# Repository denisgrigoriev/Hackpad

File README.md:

# Minimalistic Hackpad
In this project i would be design a ultra small and minimal HackPad, this removes unnessary keys and only provides keys would would be used often, for example one key could be to copy, another paste and another could be used to screenshot and and so forth.

## Goals

- Each key would be useful.
- This project focus more on aesthetic rather than functionality.
- The whole Hackpad could fit in your hand.

## Schematic & PCB design

## £3D Model

## BOM
- 4x Cherry MX Switches
- 1x EC11 Rotary Encoder
- 1x XIAO RP2040
- 1x Case (2 printed parts)
- 4x DSA Keycaps
- 2x M3x5x4 Heatset inserts
- 2x M3x12mm SHCS Bolts

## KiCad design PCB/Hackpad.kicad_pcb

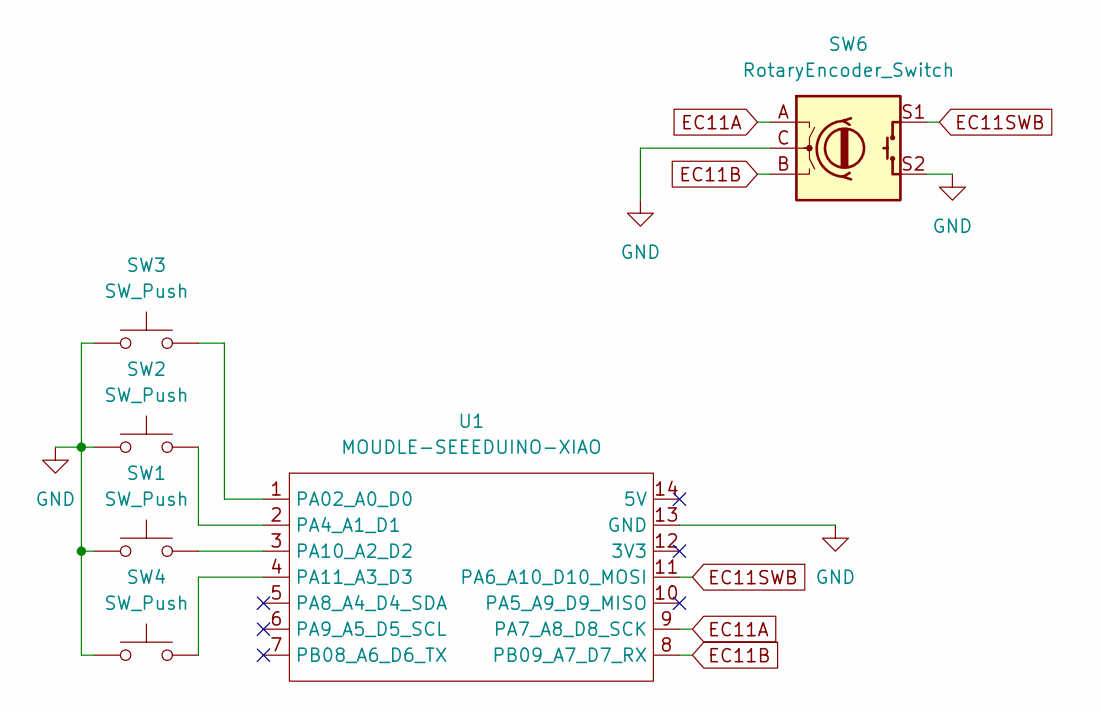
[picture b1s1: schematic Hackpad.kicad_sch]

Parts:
SW1, SW2, SW3, SW4: SW_Push; SW_Cherry_MX_1.00u_PCB
SW6: RotaryEncoder_Switch; RotaryEncoder_Alps_EC11E-Switch_Vertical_H20mm
U1: MOUDLE-SEEEDUINO-XIAO; XIAO-Generic-Hybrid-14P-2.54-21X17.8MM

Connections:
EC11A: SW6.A, U1.9 (PA7_A8_D8_SCK)
EC11B: SW6.B, U1.8 (PB09_A7_D7_RX)
EC11SWB: SW6.S1, U1.11 (PA6_A10_D10_MOSI)
GND: SW1.1, SW2.1, SW3.1, SW4.1, SW6.C, SW6.S2, U1.13 (GND)
unnamed: SW3.2, U1.1 (PA02_A0_D0)
unnamed: SW2.2, U1.2 (PA4_A1_D1)
unnamed: SW1.2, U1.3 (PA10_A2_D2)
unnamed: SW4.2, U1.4 (PA11_A3_D3)

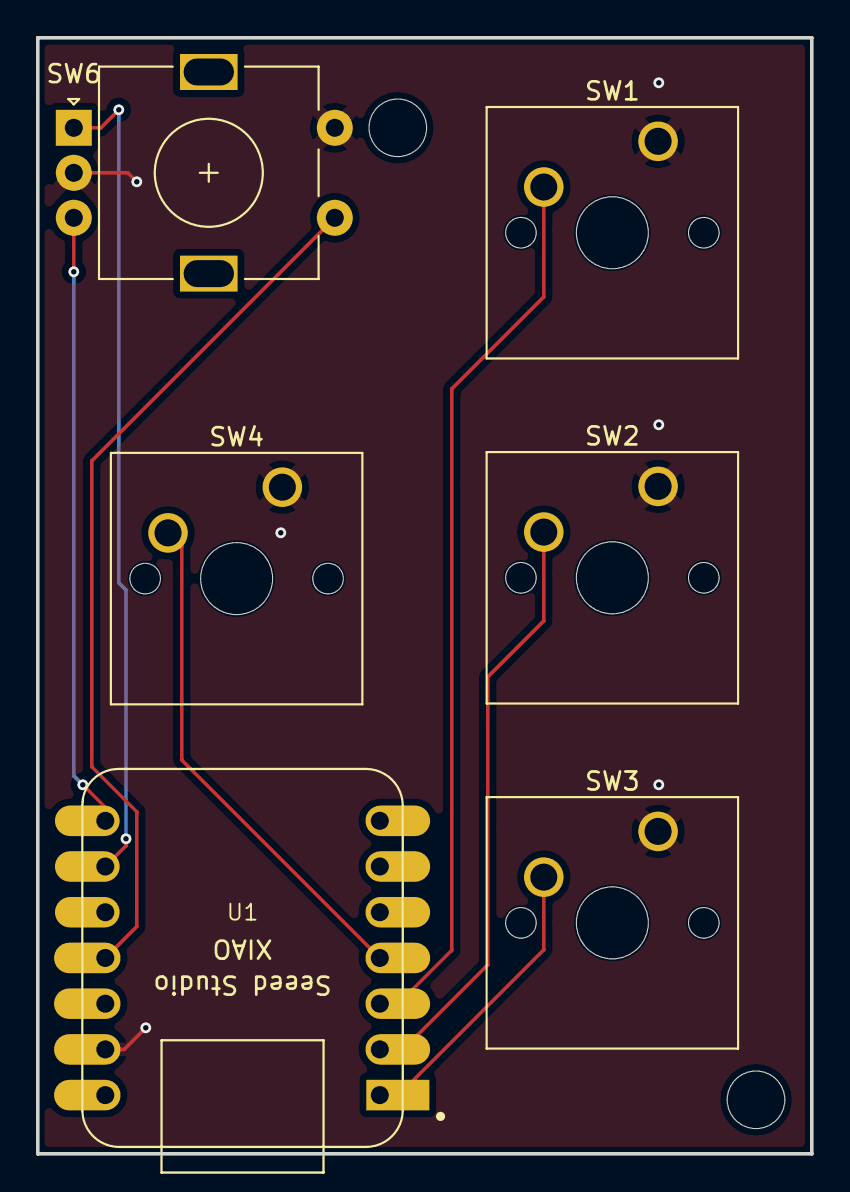
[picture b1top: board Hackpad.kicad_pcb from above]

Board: 2 copper layers, 43.0 x 62.0 mm, 6 parts (0 on the bottom side), 8 nets.
